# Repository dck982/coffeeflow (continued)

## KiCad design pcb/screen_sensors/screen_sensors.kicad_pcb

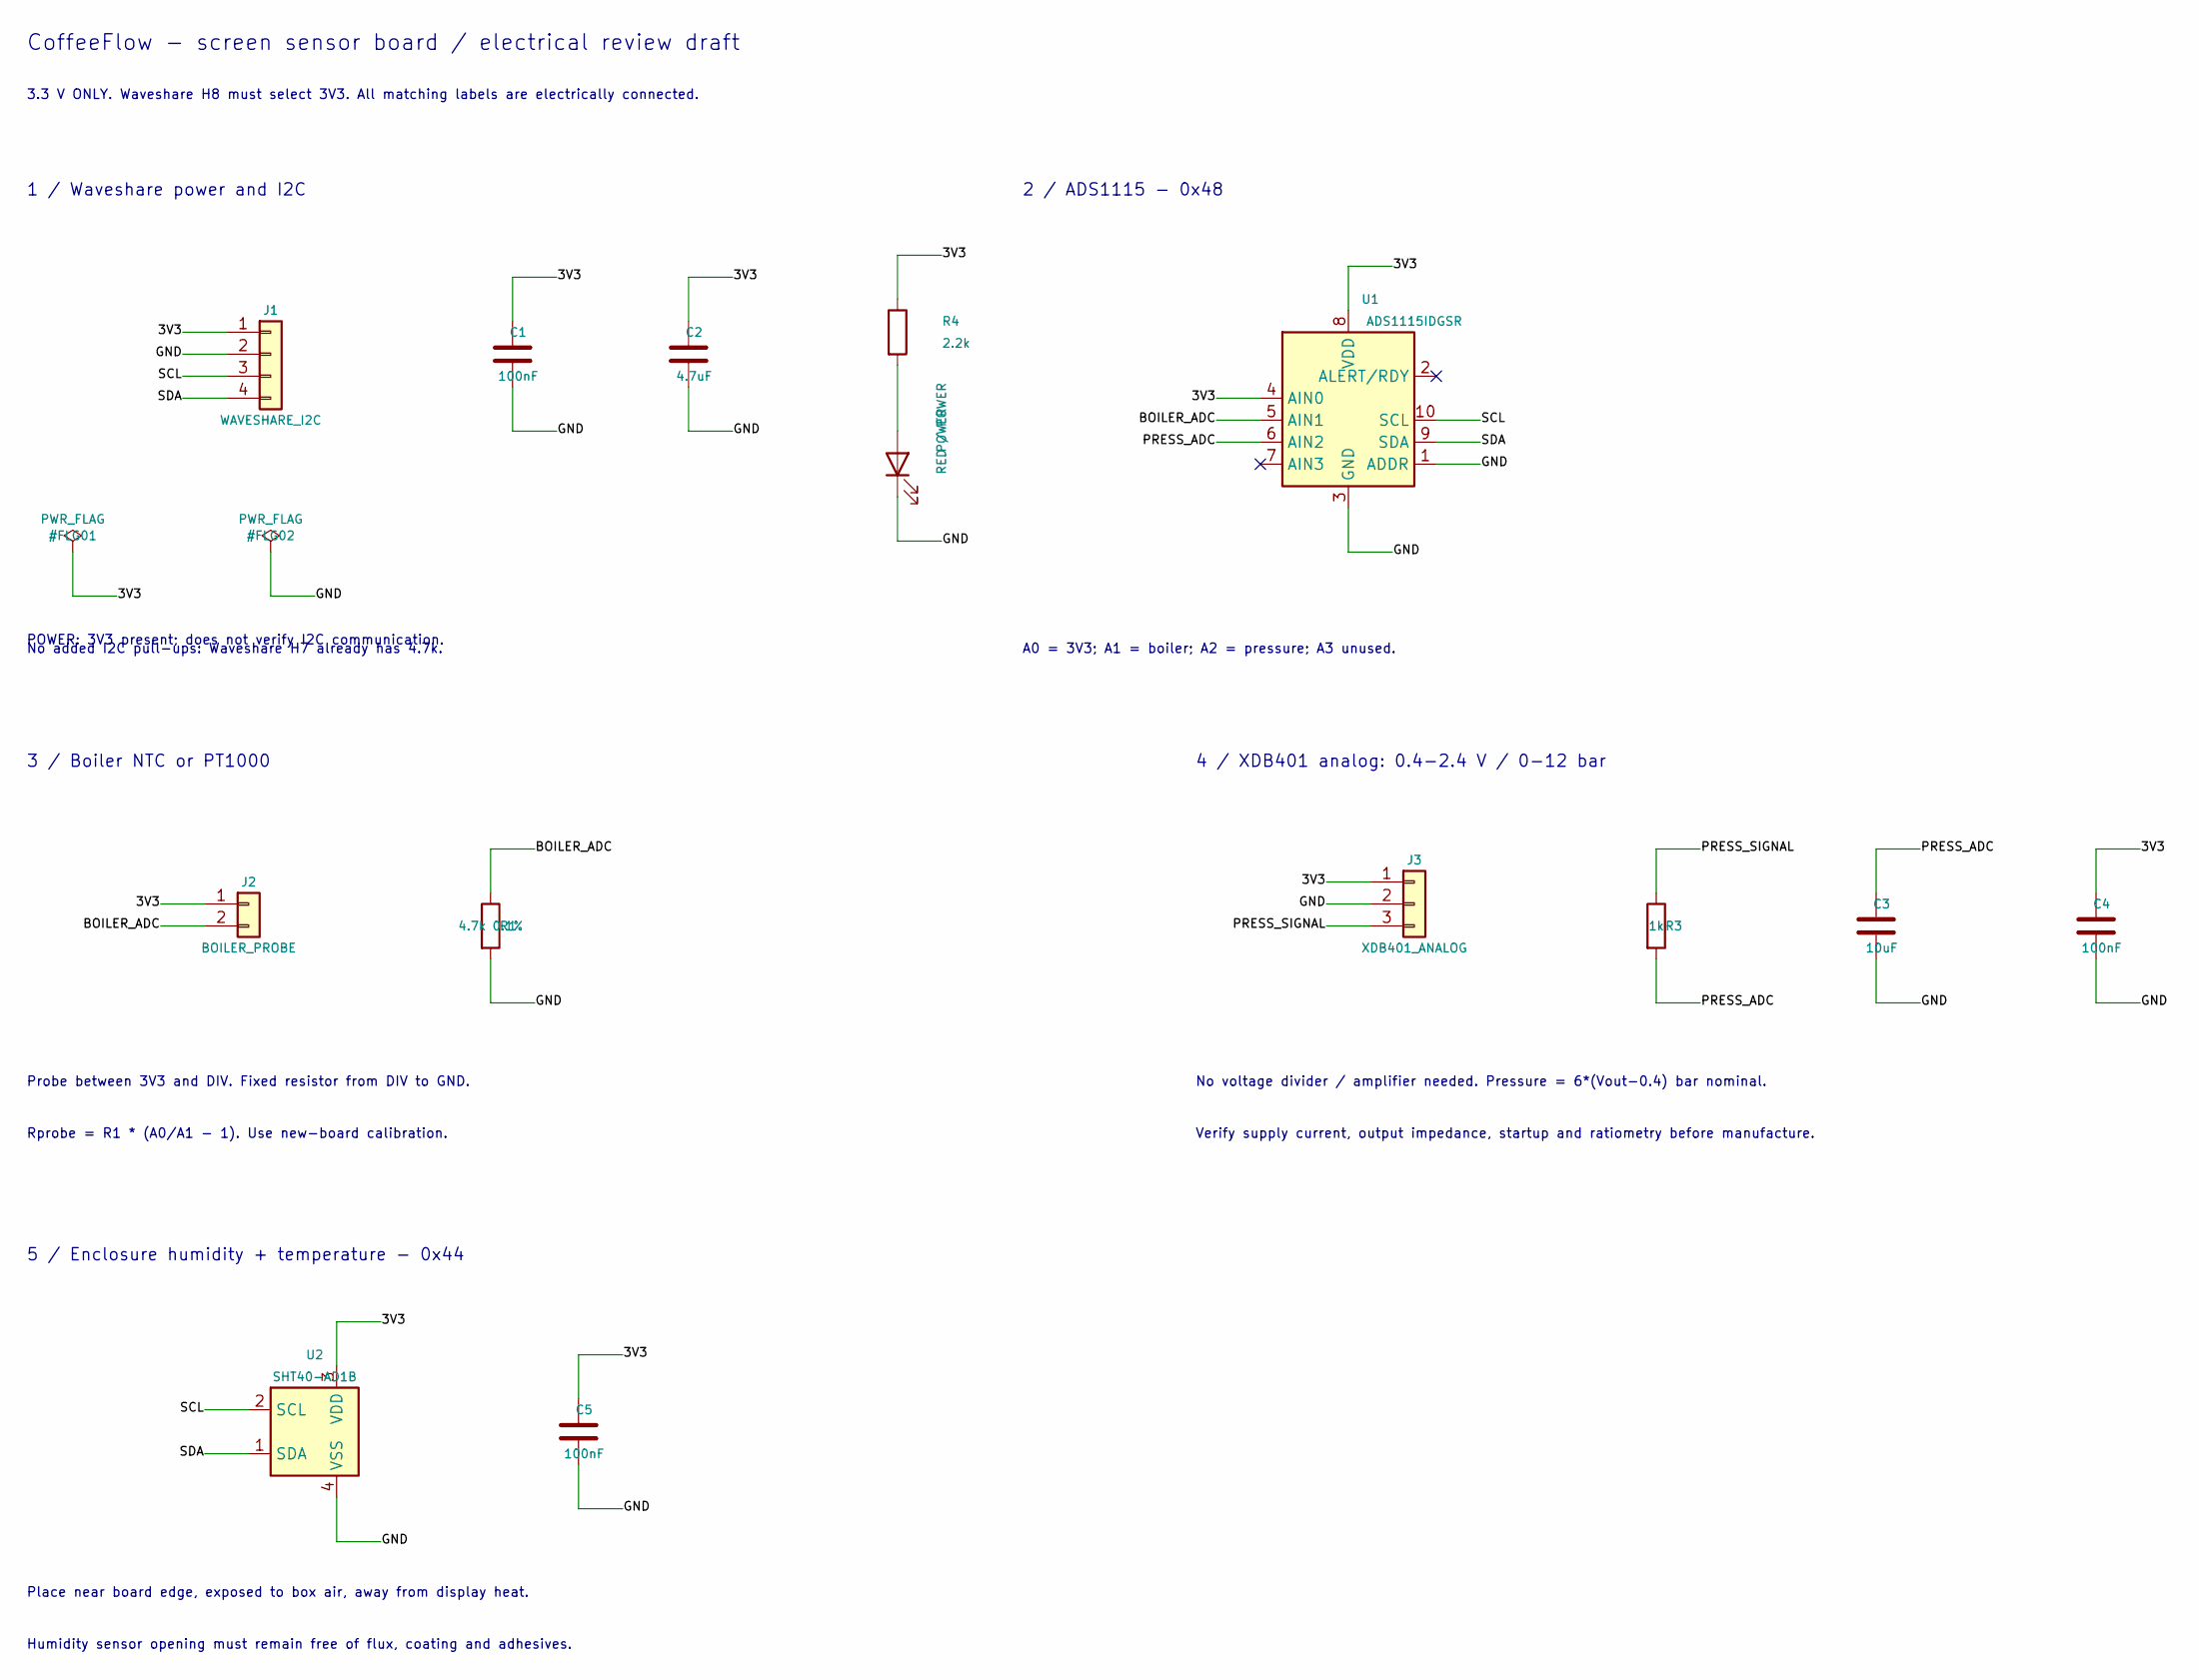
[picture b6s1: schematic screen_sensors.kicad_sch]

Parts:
C1, C4, C5: 100nF; C_0603_1608Metric; MPN CC0603KRX7R9BB104; LCSC C14663
C2: 4.7uF; C_0603_1608Metric; MPN CL10A475KO8NNNC; LCSC C19666
C3: 10uF; C_0603_1608Metric; MPN CL10A106KP8NNNC; LCSC C19702
J1: WAVESHARE_I2C; JST_XH_B4B-XH-A_1x04_P2.50mm_Vertical; MPN B4B-XH-A(LF)(SN); LCSC C144395
J2: BOILER_PROBE; JST_XH_B2B-XH-A_1x02_P2.50mm_Vertical; MPN B2B-XH-A-R(LF)(SN); LCSC C495685
J3: XDB401_ANALOG; JST_XH_B3B-XH-A_1x03_P2.50mm_Vertical; MPN B3B-XH-A(LF)(SN); LCSC C144394
POWER: RED / POWER; LED_0603_1608Metric; MPN KT-0603R; LCSC C2286
R1: 4.7k 0.1%; R_0603_1608Metric; MPN PTFR0603B4K70N9; LCSC C394547
R3: 1k; R_0603_1608Metric; MPN 0603WAF1001T5E; LCSC C21190
R4: 2.2k; R_0603_1608Metric; MPN 0603WAF2201T5E; LCSC C4190
U1: ADS1115IDGSR; TSSOP-10_3x3mm_P0.5mm; MPN ADS1115IDGSR; LCSC C37593
U2: SHT40-AD1B; Sensirion_DFN-4_1.5x1.5mm_P0.8mm_SHT4x_NoCentralPad; MPN SHT40-AD1B-R3; LCSC C2848306

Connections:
/3V3: C1.1, C2.1, C4.1, C5.1, J1.1, J2.1, J3.1, R4.1, U1.4 (AIN0), U1.8 (VDD), U2.3 (VDD)
/BOILER_ADC: J2.2, R1.1, U1.5 (AIN1)
/GND: C1.2, C2.2, C3.2, C4.2, C5.2, J1.2, J3.2, POWER.1 (K), R1.2, U1.1 (ADDR), U1.3 (GND), U2.4 (VSS)
/PRESS_ADC: C3.1, R3.2, U1.6 (AIN2)
/PRESS_SIGNAL: J3.3, R3.1
/SCL: J1.3, U1.10 (SCL), U2.2 (SCL)
/SDA: J1.4, U1.9 (SDA), U2.1 (SDA)
unnamed: POWER.2 (A), R4.2

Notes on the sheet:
CoffeeFlow - screen sensor board / electrical review draft
3.3 V ONLY. Waveshare H8 must select 3V3. All matching labels are electrically connected.
1 / Waveshare power and I2C
No added I2C pull-ups: Waveshare H7 already has 4.7k.
2 / ADS1115 - 0x48
A0 = 3V3; A1 = boiler; A2 = pressure; A3 unused.
3 / Boiler NTC or PT1000
Probe between 3V3 and DIV. Fixed resistor from DIV to GND.
Rprobe = R1 * (A0/A1 - 1). Use new-board calibration.
4 / XDB401 analog: 0.4-2.4 V / 0-12 bar
No voltage divider / amplifier needed. Pressure = 6*(Vout-0.4) bar nominal.
Verify supply current, output impedance, startup and ratiometry before manufacture.
5 / Enclosure humidity + temperature - 0x44
Place near board edge, exposed to box air, away from display heat.
Humidity sensor opening must remain free of flux, coating and adhesives.
POWER: 3V3 present; does not verify I2C communication.

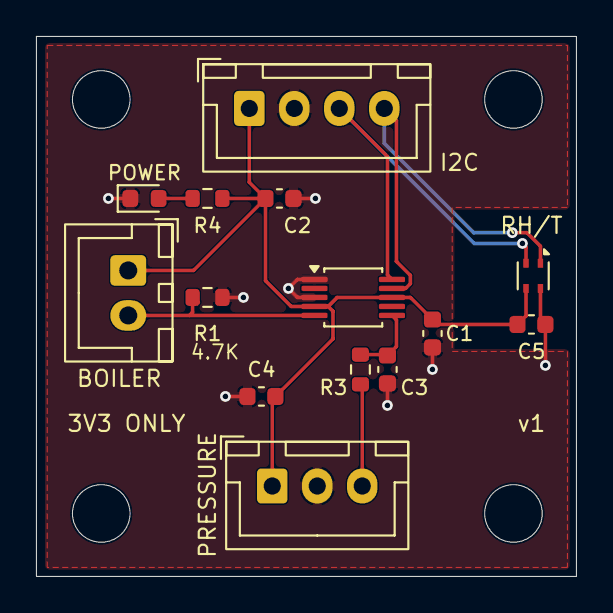
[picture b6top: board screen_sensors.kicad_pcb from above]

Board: 2 copper layers, 30.0 x 30.0 mm, 18 parts (0 on the bottom side), 8 nets.

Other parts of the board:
H1, H2, H3, H4: M3; MountingHole_3.2mm_M3

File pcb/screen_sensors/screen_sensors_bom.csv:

Reference,Value,Footprint,DNP,MPN,LCSC,Note
J1,WAVESHARE_I2C,Connector_JST:JST_XH_B4B-XH-A_1x04_P2.50mm_Vertical,False,B4B-XH-A(LF)(SN),C144395,"Pin 1 VCC/3V3, 2 GND, 3 SCL, 4 SDA; cross SDA/SCL in Waveshare cable"
C1,100nF,Capacitor_SMD:C_0603_1608Metric,False,CC0603KRX7R9BB104,C14663,At U1 VDD
C2,4.7uF,Capacitor_SMD:C_0603_1608Metric,False,CL10A475KO8NNNC,C19666,"Board bulk, X5R 16V"
U1,ADS1115IDGSR,Package_SO:TSSOP-10_3x3mm_P0.5mm,False,ADS1115IDGSR,C37593,ADDR=GND; PGA +/-4.096V; A0 measures divider supply
J2,BOILER_PROBE,Connector_JST:JST_XH_B2B-XH-A_1x02_P2.50mm_Vertical,False,B2B-XH-A-R(LF)(SN),C495685,
R1,4.7k 0.1%,Resistor_SMD:R_0603_1608Metric,False,PTFR0603B4K70N9,C394547,Precision / low TCR; calibrate new assembly
J3,XDB401_ANALOG,Connector_JST:JST_XH_B3B-XH-A_1x03_P2.50mm_Vertical,False,B3B-XH-A(LF)(SN),C144394,"Pin 1 3V3, 2 GND, 3 output; verify sensor wire colors"
R3,1k,Resistor_SMD:R_0603_1608Metric,False,0603WAF1001T5E,C21190,JLCPCB basic; 1%; provisional pressure RC filter
C3,10uF,Capacitor_SMD:C_0603_1608Metric,False,CL10A106KP8NNNC,C19702,"Input filter at ADC; 1k/10uF fc~16Hz; X5R 10V"
C4,100nF,Capacitor_SMD:C_0603_1608Metric,False,CC0603KRX7R9BB104,C14663,At pressure connector supply
U2,SHT40-AD1B,Sensor_Humidity:Sensirion_DFN-4_1.5x1.5mm_P0.8mm_SHT4x_NoCentralPad,False,SHT40-AD1B-R3,C2848306,Top-side SMT reflow with ADS1115; no board wash; address 0x44
C5,100nF,Capacitor_SMD:C_0603_1608Metric,False,CC0603KRX7R9BB104,C14663,At U2 VDD
R4,2.2k,Resistor_SMD:R_0603_1608Metric,False,0603WAF2201T5E,C4190,JLCPCB basic; 1%; power LED current limiting
POWER,RED / POWER,LED_SMD:LED_0603_1608Metric,False,KT-0603R,C2286,JLCPCB basic; red power indicator; approximately 0.6mA; pin 1 cathode to GND

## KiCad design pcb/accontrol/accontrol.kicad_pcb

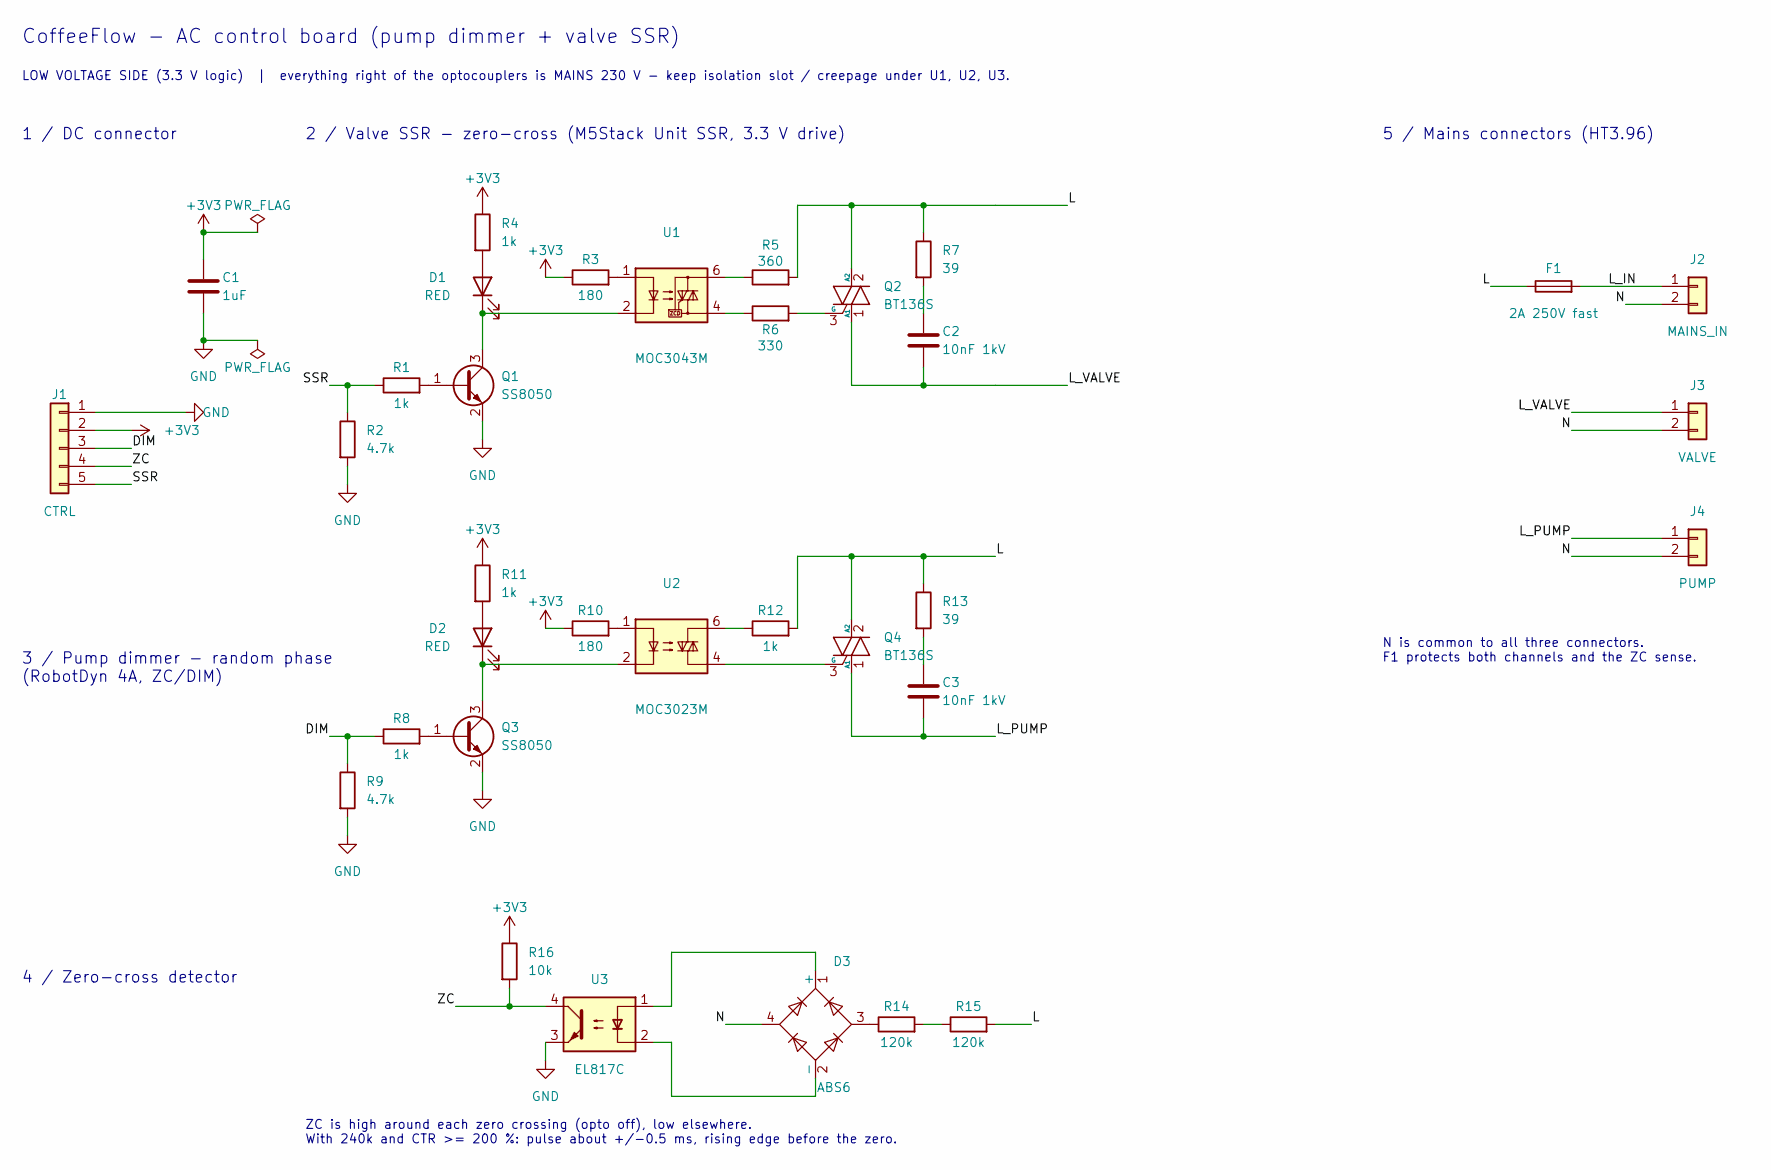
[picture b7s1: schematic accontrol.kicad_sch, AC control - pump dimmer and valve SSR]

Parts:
C1: 1uF; C_0603_1608Metric
C2, C3: 10nF 1kV; C_1206_3216Metric
D1, D2: RED; LED_0603_1608Metric
D3: ABS6; Diode_Bridge_Diotec_ABS; MPN ABS6; LCSC C48642435
F1: 2A 250V fast; F2410; MPN MF2410F2.000TM; LCSC C83797
J1: CTRL; JST_XH_B5B-XH-A_1x05_P2.50mm_Vertical; MPN B5B-XH-A(LF)(SN)
J2: MAINS_IN; CONN-TH_P3.96_HT396R-3.96-2P; MPN HT396R-3.96-2P; LCSC C577799
J3: VALVE; CONN-TH_P3.96_HT396R-3.96-2P; MPN HT396R-3.96-2P; LCSC C577799
J4: PUMP; CONN-TH_P3.96_HT396R-3.96-2P; MPN HT396R-3.96-2P; LCSC C577799
Q1, Q3: SS8050; SOT-23; MPN SS8050 (Y1)
Q2, Q4: BT136S; TO-252-2; MPN BT136S; LCSC C23427
R1, R4, R8, R11: 1k; R_0603_1608Metric
R2, R9: 4.7k; R_0603_1608Metric
R3, R10: 180; R_0603_1608Metric
R5: 360; R_1206_3216Metric
R6: 330; R_1206_3216Metric
R7: 39; R_1206_3216Metric
R12: 1k; R_1206_3216Metric
R13: 39; R_1210_3225Metric; MPN RC1210JR-0739RL; LCSC C728404
R14, R15: 120k; R_1210_3225Metric; MPN 1210W2F1203T5E; LCSC C422421
R16: 10k; R_0603_1608Metric
U1: MOC3043M; SMDIP-6_W9.53mm_Slot; MPN MOC3043M
U2: MOC3023M; SMDIP-6_W9.53mm_Slot; MPN MOC3023M
U3: EL817C; SMDIP-4_W9.53mm_Slot; MPN EL817S1(C)(TU)-F

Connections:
+3V3: C1.1, J1.2, R3.1, R4.1, R10.1, R11.1, R16.1
/DIM: J1.3, R8.1, R9.1
/L: F1.1, Q2.2 (A2), Q4.2 (A2), R5.2, R7.1, R12.2, R13.1, R15.2
/L_IN: F1.2, J2.1
/L_PUMP: C3.2, J4.1, Q4.1 (A1)
/L_VALVE: C2.2, J3.1, Q2.1 (A1)
/N: D3.4, J2.2, J3.2, J4.2
/SSR: J1.5, R1.1, R2.1
/ZC: J1.4, R16.2, U3.4
GND: C1.2, J1.1, Q1.2 (E), Q3.2 (E), R2.2, R9.2, U3.3
unnamed: C2.1, R7.2
unnamed: C3.1, R13.2
unnamed: D1.2 (A), R4.2
unnamed: D1.1 (K), Q1.3 (C), U1.2
unnamed: D2.2 (A), R11.2
unnamed: D2.1 (K), Q3.3 (C), U2.2
unnamed: D3.1 (+), U3.1
unnamed: D3.2 (-), U3.2
unnamed: D3.3, R14.1
unnamed: Q1.1 (B), R1.2
unnamed: Q2.3 (G), R6.2
unnamed: Q3.1 (B), R8.2
unnamed: Q4.3 (G), U2.4
unnamed: R3.2, U1.1
unnamed: R5.1, U1.6
unnamed: R6.1, U1.4
unnamed: R10.2, U2.1
unnamed: R12.1, U2.6
unnamed: R14.2, R15.1

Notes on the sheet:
CoffeeFlow - AC control board (pump dimmer + valve SSR)
LOW VOLTAGE SIDE (3.3 V logic) | everything right of the optocouplers is MAINS 230 V - keep isolation slot / creepage under U1, U2, U3.
1 / DC connector
2 / Valve SSR - zero-cross (M5Stack Unit SSR, 3.3 V drive)
3 / Pump dimmer - random phase (RobotDyn 4A, ZC/DIM)
4 / Zero-cross detector
5 / Mains connectors (HT3.96)
ZC is high around each zero crossing (opto off), low elsewhere. With 240k and CTR >= 200 %: pulse about +/-0.5 ms, rising edge before the zero.
N is common to all three connectors. F1 protects both channels and the ZC sense.

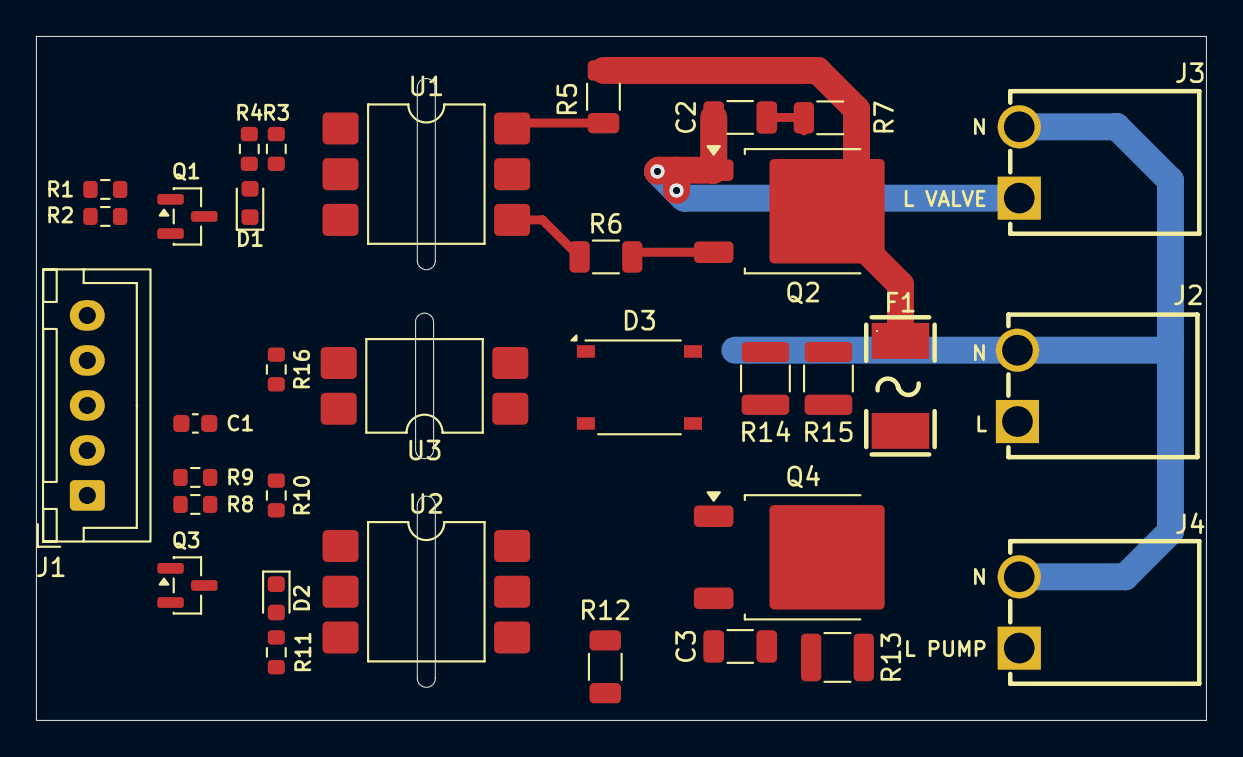
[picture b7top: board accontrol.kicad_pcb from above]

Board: 2 copper layers, 65.0 x 38.0 mm, 34 parts (0 on the bottom side), 29 nets.

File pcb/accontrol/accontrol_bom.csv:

"Reference","Value","Footprint","DNP","MPN","LCSC","Note"
"C1","1uF","Capacitor_SMD:C_0603_1608Metric","","","","3V3 decoupling at J1"
"C2","10nF 1kV","Capacitor_SMD:C_1206_3216Metric","","","","Snubber, X7R 1000 V"
"C3","10nF 1kV","Capacitor_SMD:C_1206_3216Metric","","","","Snubber, X7R 1000 V"
"D1","RED","LED_SMD:LED_0603_1608Metric","","","","Channel indicator"
"D2","RED","LED_SMD:LED_0603_1608Metric","","","","Channel indicator"
"D3","ABS6","Diode_SMD:Diode_Bridge_Diotec_ABS","","ABS6","C48642435","Hongjiacheng ABS6, 600 V, ABS package (4 mm pitch)"
"F1","2A 250V fast","Accontrol_Local:F2410","","MF2410F2.000TM","C83797","AEM 2410 fast, 100 A breaking at 250 VAC"
"J1","CTRL","Connector_JST:JST_XH_B5B-XH-A_1x05_P2.50mm_Vertical","","B5B-XH-A(LF)(SN)","","1 GND, 2 3V3, 3 DIM, 4 ZC, 5 SSR"
"J2","MAINS_IN","Accontrol_Local:CONN-TH_P3.96_HT396R-3.96-2P","","HT396R-3.96-2P","C577799","1 L, 2 N"
"J3","VALVE","Accontrol_Local:CONN-TH_P3.96_HT396R-3.96-2P","","HT396R-3.96-2P","C577799","1 L (switched), 2 N"
"J4","PUMP","Accontrol_Local:CONN-TH_P3.96_HT396R-3.96-2P","","HT396R-3.96-2P","C577799","1 L (switched), 2 N"
"Q1","SS8050","Package_TO_SOT_SMD:SOT-23","","SS8050 (Y1)","","SOT-23 pinout 1 B, 2 E, 3 C"
"Q2","BT136S","Package_TO_SOT_SMD:TO-252-2","","BT136S","C23427","DPAK: 1 MT1, 2 MT2 (tab), 3 G"
"Q3","SS8050","Package_TO_SOT_SMD:SOT-23","","SS8050 (Y1)","","SOT-23 pinout 1 B, 2 E, 3 C"
"Q4","BT136S","Package_TO_SOT_SMD:TO-252-2","","BT136S","C23427","DPAK: 1 MT1, 2 MT2 (tab), 3 G"
"R1","1k","Resistor_SMD:R_0603_1608Metric","","","","Base resistor"
"R2","4.7k","Resistor_SMD:R_0603_1608Metric","","","","Holds the channel off when the cable is unplugged"
"R3","180","Resistor_SMD:R_0603_1608Metric","","","","MOC LED: (3.3-1.2-0.1)/180 = 11 mA typ, >= 8 mA worst case"
"R4","1k","Resistor_SMD:R_0603_1608Metric","","","","Indicator LED ~1.2 mA"
"R5","360","Resistor_SMD:R_1206_3216Metric","","","","MT2 series resistor (M5Stack design)"
"R6","330","Resistor_SMD:R_1206_3216Metric","","","","Gate series resistor (M5Stack design)"
"R7","39","Resistor_SMD:R_1206_3216Metric","","","","Snubber"
"R8","1k","Resistor_SMD:R_0603_1608Metric","","","","Base resistor"
"R9","4.7k","Resistor_SMD:R_0603_1608Metric","","","","Holds the channel off when the cable is unplugged"
"R10","180","Resistor_SMD:R_0603_1608Metric","","","","MOC LED: (3.3-1.2-0.1)/180 = 11 mA typ, >= 8 mA worst case"
"R11","1k","Resistor_SMD:R_0603_1608Metric","","","","Indicator LED ~1.2 mA"
"R12","1k","Resistor_SMD:R_1206_3216Metric","","","","MT2 series resistor, gate driven directly (RobotDyn design)"
"R13","39","Resistor_SMD:R_1210_3225Metric","","RC1210JR-0739RL","C728404","Snubber, 1210 for the C3 discharge at each firing"
"R14","120k","Resistor_SMD:R_1210_3225Metric","","1210W2F1203T5E","C422421","ZC sense, 2 x 120k 1210 in series = 240k: 0.11 W (22 %) and 160 V peak each"
"R15","120k","Resistor_SMD:R_1210_3225Metric","","1210W2F1203T5E","C422421","ZC sense, see R14"
"R16","10k","Resistor_SMD:R_0603_1608Metric","","","","ZC pull-up (RobotDyn value)"
"U1","MOC3043M","Accontrol_Local:SMDIP-6_W9.53mm_Slot","","MOC3043M","","IFT max 5 mA; ~11 mA with 180R at 3.3 V"
"U2","MOC3023M","Accontrol_Local:SMDIP-6_W9.53mm_Slot","","MOC3023M","","IFT max 5 mA; ~11 mA with 180R at 3.3 V"
"U3","EL817C","Accontrol_Local:SMDIP-4_W9.53mm_Slot","","EL817S1(C)(TU)-F","","CTR rank C 200-400 %"
